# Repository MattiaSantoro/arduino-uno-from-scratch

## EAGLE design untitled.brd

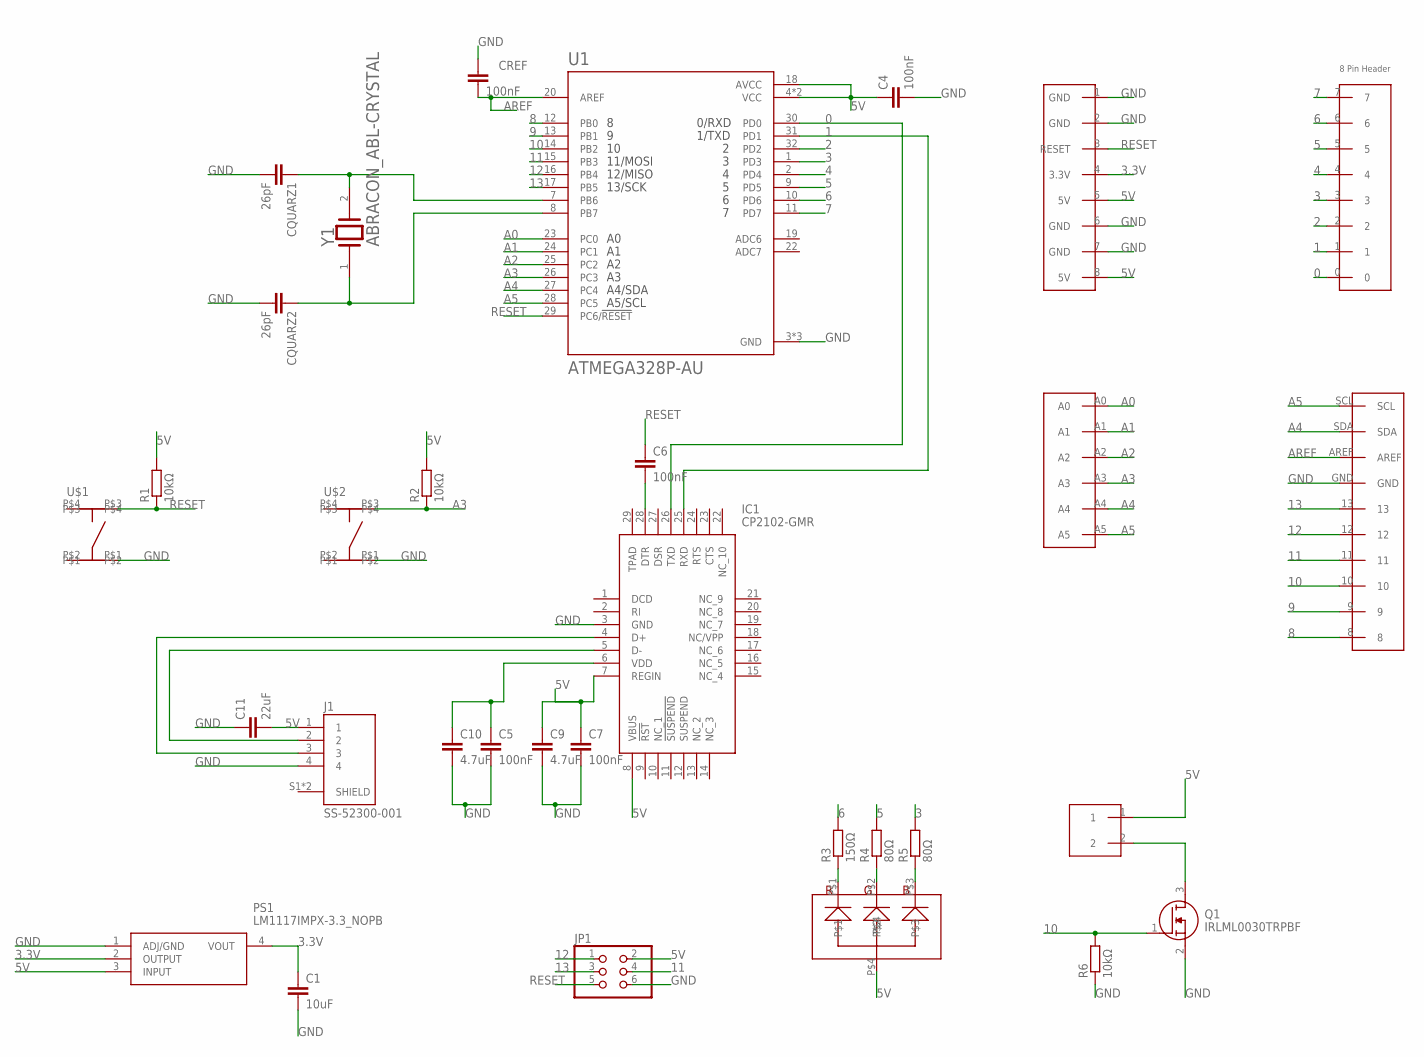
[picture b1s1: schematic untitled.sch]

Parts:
C1: 10uF; C1206
C4, C5, C6, C7: 100nF; C1206
C9, C10: 4.7uF; C1206
C11: 22uF; C1206
CQUARZ1, CQUARZ2: 26pF; C1206
CREF: 100nF; C1206
IC1: CP2102-GMR; QFN50P500X500X100-29N
J1: SS-52300-001; BEL_SS-52300-001
JP1: PINHD-2X3; 2X03
PS1: LM1117IMPX-3.3_NOPB; SOT230P700X180-4N
Q1: IRLML0030TRPBF; SOT95P237X112-3N
R1, R2, R6: 10kΩ; R1206
R3: 150Ω; R1206
R4, R5: 80Ω; R1206
U1: ATMEGA328P-AU; QFP80P900X900X120-32N
U$1, U$2: TASTER_9315
U$3: RGBLED_6723; RGBLED
U$4: 6_PIN_HEADER_ARDUINO_UNO
U$5: 8_PIN_HEADER_ARDUINO_UNO_1
U$6: 8_PIN_HEADER_ARDUINO_UNO_2
U$7: 10_PIN_HEADER_ARDUINO_UNO
U$8: JSTPH2PST; B2B-PH-K-S
Y1: ABRACON_ABL-CRYSTALABRACON_ABL-16.000MHZ-B2_0_0; HC-49/US

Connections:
0: IC1.26 (TXD), U1.30 (PD0), U$5.0
1: IC1.25 (RXD), U1.31 (PD1), U$5.1
2: U1.32 (PD2), U$5.2
3: R5.2, U1.1 (PD3), U$5.3
3.3V: C1.1, PS1.2 (OUTPUT), PS1.4 (VOUT), U$6.4 (3.3V)
4: U1.2 (PD4), U$5.4
5: R4.2, U1.9 (PD5), U$5.5
5V: C4.1, C7.1, C9.1, C11.2, IC1.7 (REGIN), IC1.8 (VBUS), J1.1, JP1.2, PS1.3 (INPUT), R1.2, R2.2, U1.4 (VCC), U1.6 (VCC), U1.18 (AVCC), U$3.P$4, U$6.5 (5V), U$6.8 (5V), U$8.1
6: R3.2, U1.10 (PD6), U$5.6
7: U1.11 (PD7), U$5.7
8: U1.12 (PB0), U$7.8
9: U1.13 (PB1), U$7.9
10: Q1.1 (G), R6.2, U1.14 (PB2), U$7.10
11: JP1.4, U1.15 (PB3), U$7.11
12: JP1.1, U1.16 (PB4), U$7.12
13: JP1.3, U1.17 (PB5), U$7.13
A0: U1.23 (PC0), U$4.A0
A1: U1.24 (PC1), U$4.A1
A2: U1.25 (PC2), U$4.A2
A3: R2.1, U1.26 (PC3), U$2.P$3, U$4.A3
A4: U1.27 (PC4), U$4.A4, U$7.SDA
A5: U1.28 (PC5), U$4.A5, U$7.SCL
AREF: CREF.2, U1.20 (AREF), U$7.AREF
GND: C1.2, C4.2, C5.2, C7.2, C9.2, C10.2, C11.1, CQUARZ1.2, CQUARZ2.2, CREF.1, IC1.3 (GND), J1.4, JP1.6, PS1.1 (ADJ/GND), Q1.2 (S), R6.1, U1.3 (GND), U1.5 (GND), U1.21 (GND), U$1.P$1, U$2.P$1, U$6.1 (GND), U$6.2 (GND), U$6.6 (GND), U$6.7 (GND), U$7.GND
unnamed: Q1.3 (D), U$8.2
unnamed: CQUARZ2.1, U1.8 (PB7), Y1.1
unnamed: CQUARZ1.1, U1.7 (PB6), Y1.2
unnamed: IC1.5 (D-), J1.2
unnamed: IC1.4 (D+), J1.3
unnamed: C5.1, C10.1, IC1.6 (VDD)
unnamed: C6.2, IC1.28 (DTR)
unnamed: R3.1, U$3.P$1
unnamed: R4.1, U$3.P$2
unnamed: R5.1, U$3.P$3
RESET: C6.1, JP1.5, R1.1, U1.29 (PC6/!RESET), U$1.P$3, U$6.3 (RESET)

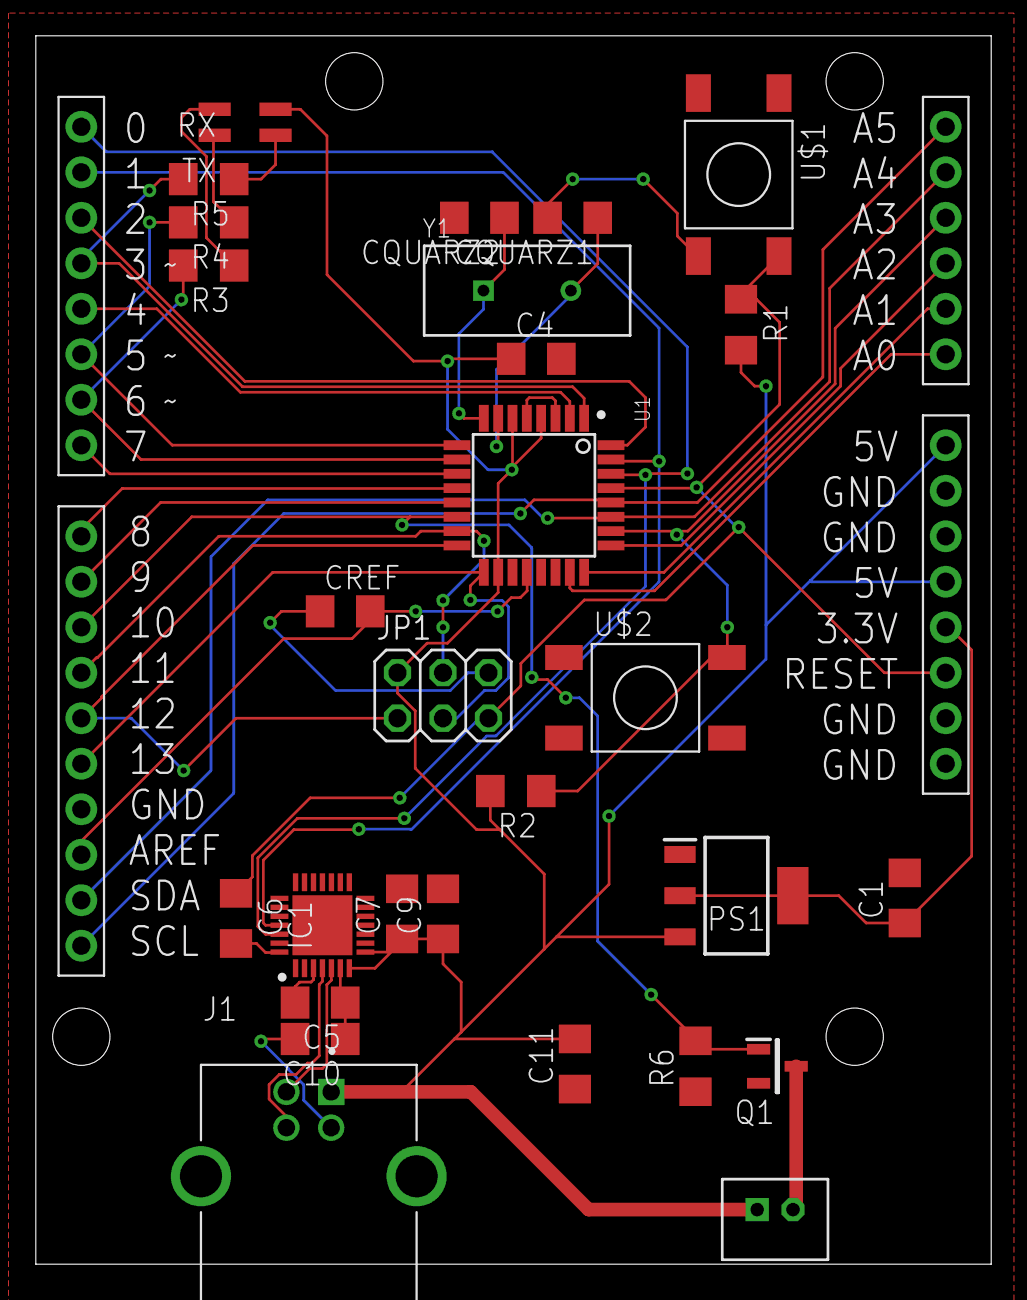
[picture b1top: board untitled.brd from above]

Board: 2 copper layers, 53.3 x 68.6 mm, 32 parts (0 on the bottom side), 35 nets.
